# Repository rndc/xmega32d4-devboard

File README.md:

# xmega32d4-devboard
This is just another Atmel ATxmega32D4 development board with onboard 3.3V LDO and 32.768 kHz xtal. For further information, please read the [Atmel ATxmega32D4 datasheet](http://www.atmel.com/images/Atmel-8135-8-and-16-bit-AVR-microcontroller-ATxmega16D4-32D4-64D4-128D4_datasheet.pdf).

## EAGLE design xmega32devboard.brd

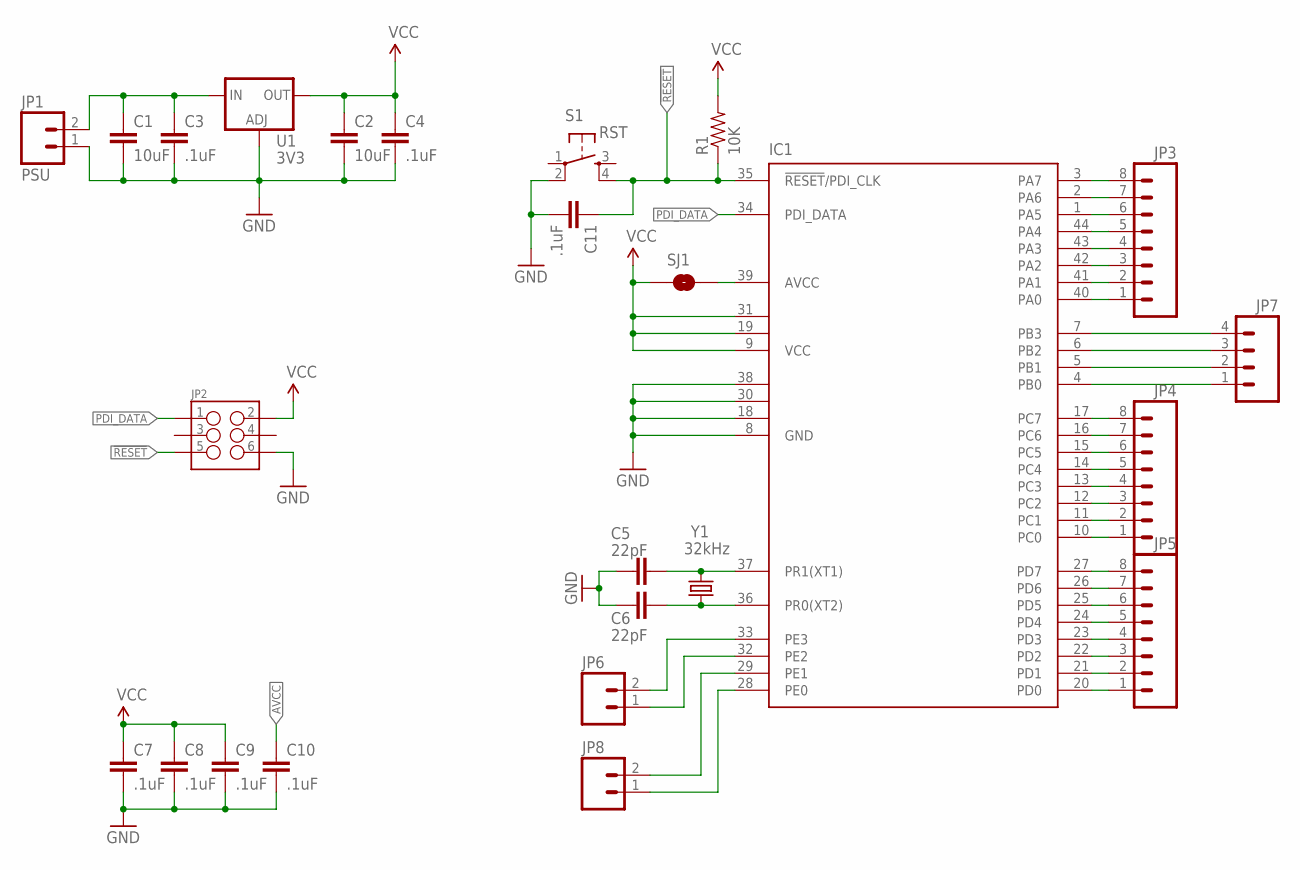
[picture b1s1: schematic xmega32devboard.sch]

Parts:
C1, C2: 10uF; 0603-CAP
C3, C4, C7, C8, C9, C10, C11: .1uF; 0805
C5, C6: 22pF; 0805
IC1: XMEGA16A4A; TQFP44
JP1: PSU; 1X02
JP2: M03X2NO_SILK; 2X3-NS
JP3, JP4, JP5: M081X08; 1X08
JP6, JP8: M02PTH; 1X02
JP7: M04PTH; 1X04
R1: 10K; 0603-RES
S1: RST; TACTILE-SWITCH-SMD
SJ1: JUMPER-PAD-2-NO; PAD-JUMPER-2-NO_NO_SILK
U1: 3V3; SOT223
Y1: 32kHz; TC38H

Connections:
!RESET: C11.1, IC1.35 (!RESET!/PDI_CLK), JP2.5, R1.1, S1.4
AVCC: C10.1, IC1.39 (AVCC), SJ1.2
GND: C1.2, C2.2, C3.2, C4.2, C5.1, C6.1, C7.2, C8.2, C9.2, C10.2, C11.2, IC1.8 (GND), IC1.18 (GND1), IC1.30 (GND2), IC1.38 (GND3), JP1.1, JP2.6, S1.2, U1.1 (ADJ)
unnamed: C1.1, C3.1, JP1.2, U1.3 (IN)
unnamed: C6.2, IC1.36 (PR0(XT2)), Y1.2
unnamed: C5.2, IC1.37 (PR1(XT1)), Y1.1
unnamed: IC1.20 (PD0), JP5.1
unnamed: IC1.21 (PD1), JP5.2
unnamed: IC1.22 (PD2), JP5.3
unnamed: IC1.23 (PD3), JP5.4
unnamed: IC1.24 (PD4), JP5.5
unnamed: IC1.25 (PD5), JP5.6
unnamed: IC1.26 (PD6), JP5.7
unnamed: IC1.27 (PD7), JP5.8
unnamed: IC1.40 (PA0), JP3.1
unnamed: IC1.41 (PA1), JP3.2
unnamed: IC1.42 (PA2), JP3.3
unnamed: IC1.43 (PA3), JP3.4
unnamed: IC1.44 (PA4), JP3.5
unnamed: IC1.1 (PA5), JP3.6
unnamed: IC1.2 (PA6), JP3.7
unnamed: IC1.3 (PA7), JP3.8
unnamed: IC1.17 (PC7), JP4.8
unnamed: IC1.16 (PC6), JP4.7
unnamed: IC1.15 (PC5), JP4.6
unnamed: IC1.14 (PC4), JP4.5
unnamed: IC1.13 (PC3), JP4.4
unnamed: IC1.12 (PC2), JP4.3
unnamed: IC1.11 (PC1), JP4.2
unnamed: IC1.10 (PC0), JP4.1
unnamed: IC1.33 (PE3), JP6.2
unnamed: IC1.32 (PE2), JP6.1
unnamed: IC1.29 (PE1), JP8.2
unnamed: IC1.28 (PE0), JP8.1
PB0: IC1.4 (PB0), JP7.1
PB1: IC1.5 (PB1), JP7.2
PB2: IC1.6 (PB2), JP7.3
PB3: IC1.7 (PB3), JP7.4
PDI_DATA: IC1.34 (PDI_DATA), JP2.1
VCC: C2.1, C4.1, C7.1, C8.1, C9.1, IC1.9 (VCC), IC1.19 (VCC1), IC1.31 (VCC2), JP2.2, R1.2, SJ1.1, U1.2 (OUT)

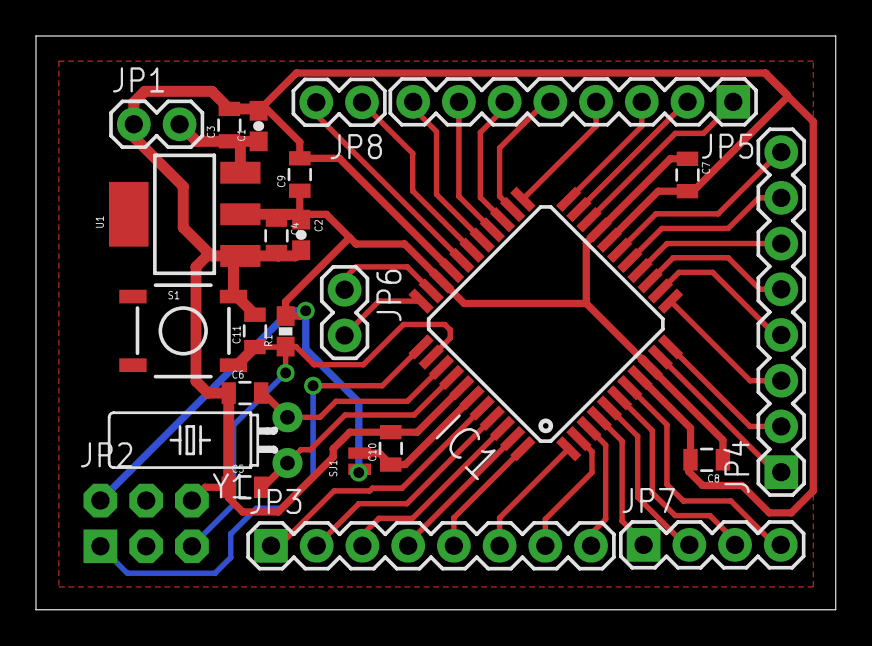
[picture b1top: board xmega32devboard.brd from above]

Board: 2 copper layers, 44.4 x 31.9 mm, 25 parts (0 on the bottom side), 40 nets.

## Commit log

2015-02-04 :sparkles: Initial commit

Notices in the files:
parts and their libraries:
SparkFun-Capacitors: Licensing: Creative Commons ShareAlike 4.0 International - https://creativecommons.org/licenses/by-sa/4.0
